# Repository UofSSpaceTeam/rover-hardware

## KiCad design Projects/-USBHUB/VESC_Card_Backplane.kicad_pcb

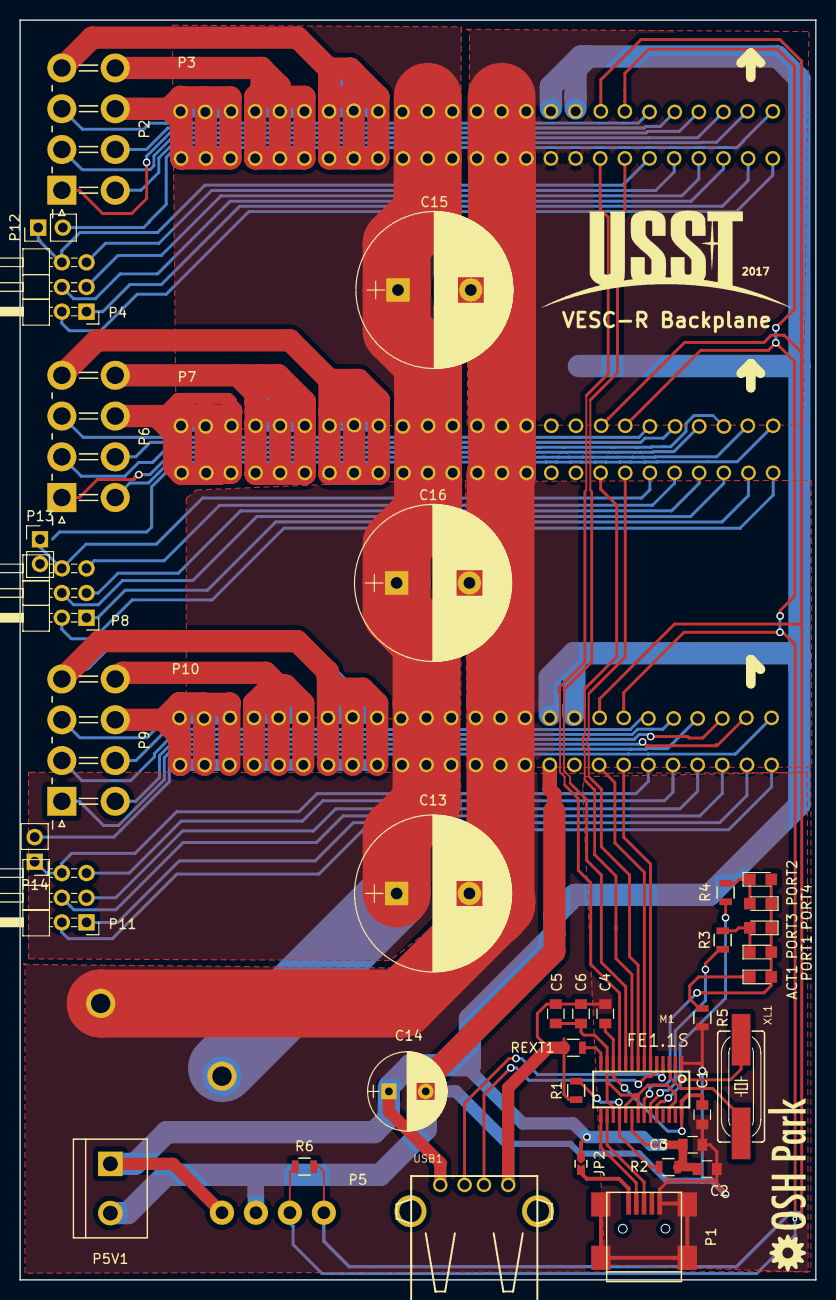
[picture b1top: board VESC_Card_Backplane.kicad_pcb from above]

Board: 2 copper layers, 82.0 x 129.8 mm, 42 parts (1 on the bottom side), 74 nets.

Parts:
ACT1: LED_0805
C1, C2, C5: 10uF; C_0805
C3, C4, C6: 0.1uF; C_0805
C13, C15, C16: 2200u; CP_Radial_D16.0mm_P7.50mm
C14: 100u; CP_Radial_D8.0mm_P3.80mm
JP2: J; J_0603
M1: FE1.1S; FE1.1S_SSOP-28
P1: USB_OTG; USB_Mini-B
P2, P6, P9: EC90_Flat; Molex_MiniFit-JR-5569-08A2_2x04x4.20mm_Angled_Overhang
P3, P7, P10: AMP17614426-2_EDGE; TE2007088-1_Backplane2
P4, P8, P11: CONN_01X06; Pin_Header_Angled_2x03_Pitch2.54mm
P5: CONN_01X04; Molex_39502_1004R
P5V1: CONN_01X02; Molex_39531_1002
P12, P13, P14: CONN_01X02; Pin_Header_Straight_1x02_Pitch2.54mm
PBAT1: CONN_01X02; Phoenix_Contact_PLA5
PORT1, PORT2, PORT3, PORT4: LED_0805
R1: 100K; R_0805
R2: 47K; R_0805
R3, R4, R5: 330; R_0805
R6: 120; R_0805
REXT1: 2.7K; R_0805
USB1: USB-TYPA; USB_A_PTH_AMP787616-1
XL1: 12MHz; HC49UP_SMT_Crystal

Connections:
+5V: C2.1, C3.1, C14.1, JP2.1, M1.20, P3.6, P3.7, P5.1, P5V1.1, P7.6, P7.7, P10.6, P10.7, R2.1, USB1.VBUS
/CANH: P3.8, P5.4, P7.8, P10.8, R6.2
/CAN_Bus/CANL: P3.9, P5.3, P7.9, P10.9, R6.1
/DM_4: M1.4, USB1.D-
/DP_4: M1.5, USB1.D+
/Motor_Controller_A/GND_AUX: P3.21, P4.6, P12.1
/Motor_Controller_A/H1: P2.1, P3.12
/Motor_Controller_A/H2: P2.2, P3.13
/Motor_Controller_A/H3: P2.5, P3.14
/Motor_Controller_A/W: P2.7, P3.1, P3.30
/Motor_Controller_A/X: P2.8, P3.2, P3.29
/Motor_Controller_A/Y: P2.4, P3.3, P3.28
/Motor_Controller_B/GND_AUX: P7.21, P8.6, P13.1
/Motor_Controller_B/H1: P6.1, P7.12
/Motor_Controller_B/H2: P6.2, P7.13
/Motor_Controller_B/H3: P6.5, P7.14
/Motor_Controller_B/W: P6.7, P7.1, P7.30
/Motor_Controller_B/X: P6.8, P7.2, P7.29
/Motor_Controller_B/Y: P6.4, P7.3, P7.28
/Motor_Controller_C/GND_AUX: P10.21, P11.6, P14.1
/Motor_Controller_C/H1: P9.1, P10.12
/Motor_Controller_C/H2: P9.2, P10.13
/Motor_Controller_C/H3: P9.5, P10.14
/Motor_Controller_C/W: P9.7, P10.1, P10.30
/Motor_Controller_C/X: P9.8, P10.2, P10.29
/Motor_Controller_C/Y: P9.4, P10.3, P10.28
/PGND: C13.2, C15.2, C16.2, P3.5, P3.24, P3.25, P3.26, P7.5, P7.24, P7.25, P7.26, P10.5, P10.26, PBAT1.2
/USB_DM_1: M1.10, P3.22
/USB_DM_2: M1.8, P7.22
/USB_DM_3: M1.6, P10.22
/USB_DP_1: M1.11, P3.23
/USB_DP_2: M1.9, P7.23
/USB_DP_3: M1.7, P10.23
/USB_Hub/DM_U: M1.15, P1.2
/USB_Hub/DP_U: M1.16, P1.3
/USB_Hub/N$1: M1.14, REXT1.2
/USB_Hub/N$6: PORT2.1, PORT4.2, R4.2
/USB_Hub/N$7: M1.2, XL1.2
/USB_Hub/N$8: C1.1, C4.1, M1.12, M1.28
/USB_Hub/N$9: M1.3, XL1.1
/USB_Hub/N$13: M1.18, R1.1, R2.2
/USB_Hub/N$20: PORT1.1, PORT3.2, R3.2
/USB_Hub/N$22: ACT1.1, R5.1
/USB_Hub/N$23: M1.23, R3.1
/USB_Hub/N$24: M1.24, R4.1
/USB_Hub/N$25: ACT1.2, M1.22, PORT1.2, PORT2.2, PORT3.1, PORT4.1
/VBAT: C13.1, C15.1, C16.1, P3.4, P3.27, P7.4, P7.27, P10.4, P10.27, PBAT1.1
GND: C1.2, C2.2, C3.2, C4.2, C5.2, C6.2, C14.2, M1.1, P1.5, P1.6, P5.2, P5V1.2, P10.24, P10.25, R1.2, R5.2, REXT1.1, USB1.GND
unnamed: JP2.2, P1.1
unnamed: P2.3, P3.10
unnamed: P2.6, P3.11
unnamed: P3.16, P4.2
unnamed: P3.17, P4.1
unnamed: P3.18, P4.4
unnamed: P3.19, P4.3
unnamed: P3.20, P4.5
unnamed: P6.3, P7.10
unnamed: P6.6, P7.11
unnamed: P7.16, P8.2
unnamed: P7.17, P8.1
unnamed: P7.18, P8.4
unnamed: P7.19, P8.3
unnamed: P7.20, P8.5
unnamed: P9.3, P10.10
unnamed: P9.6, P10.11
unnamed: P10.15, P14.2
unnamed: P10.16, P11.2
unnamed: P10.17, P11.1
unnamed: P10.18, P11.4
unnamed: P10.19, P11.3
unnamed: P10.20, P11.5
unnamed: P3.15, P12.2
unnamed: P7.15, P13.2
VDD: C5.1, C6.1, M1.13, M1.17, M1.19, M1.21, M1.26

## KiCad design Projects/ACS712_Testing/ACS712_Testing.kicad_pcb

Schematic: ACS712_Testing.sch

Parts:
P1: CONN_01X04; Pin_Header_Straight_1x04_Pitch2.54mm
R1: 10k; R_0805_HandSoldering
TH1: THERMISTOR; R_0805_HandSoldering
W1, W2: TEST_1P; Testpad_large

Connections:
+3V3: P1.1, TH1.1; also elsewhere on the board
/ACS712/ALL_I+: W1.1, W2.1; also elsewhere on the board
/ACS712/ISENSE_OUT: P1.3; also elsewhere on the board
GND: P1.4, R1.2; also elsewhere on the board
unnamed: P1.2, R1.1, TH1.2

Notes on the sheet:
To Do: - Power Connectors (In and Out) - Logic and Power Connector (3V3 and GND and ISENSE_OUT) - NTC Temperature Sensor Circuit (http://www.petervis.com/GCSE_Design_and_Technology_Electronic_Products/Potential_Divider/Potential_Divider_with_Thermistor.html) - Connect I+ and I- to Power

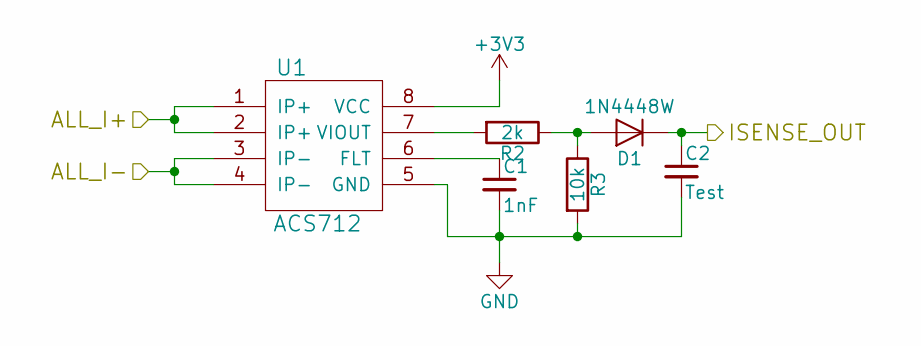
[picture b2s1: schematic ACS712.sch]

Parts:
C1: 1nF; C_1210
C2: Test; C_1210
D1: 1N4448W; D_SOD-123
R2: 2k; R_0805_HandSoldering
R3: 10k; R_0805_HandSoldering
U1: ACS712; SOIC-8_3.9x4.9mm_Pitch1.27mm

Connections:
+3V3: U1.8 (VCC); also elsewhere on the board
/ACS712/ALL_I+: U1.1 (IP+), U1.2 (IP+), U1.3 (IP-), U1.4 (IP-); also elsewhere on the board
/ACS712/ISENSE_OUT: C2.1, D1.1 (K); also elsewhere on the board
GND: C1.2, C2.2, R3.2, U1.5 (GND); also elsewhere on the board
unnamed: C1.1, U1.6 (FLT)
unnamed: D1.2 (A), R2.1, R3.1
unnamed: R2.2, U1.7 (VIOUT)

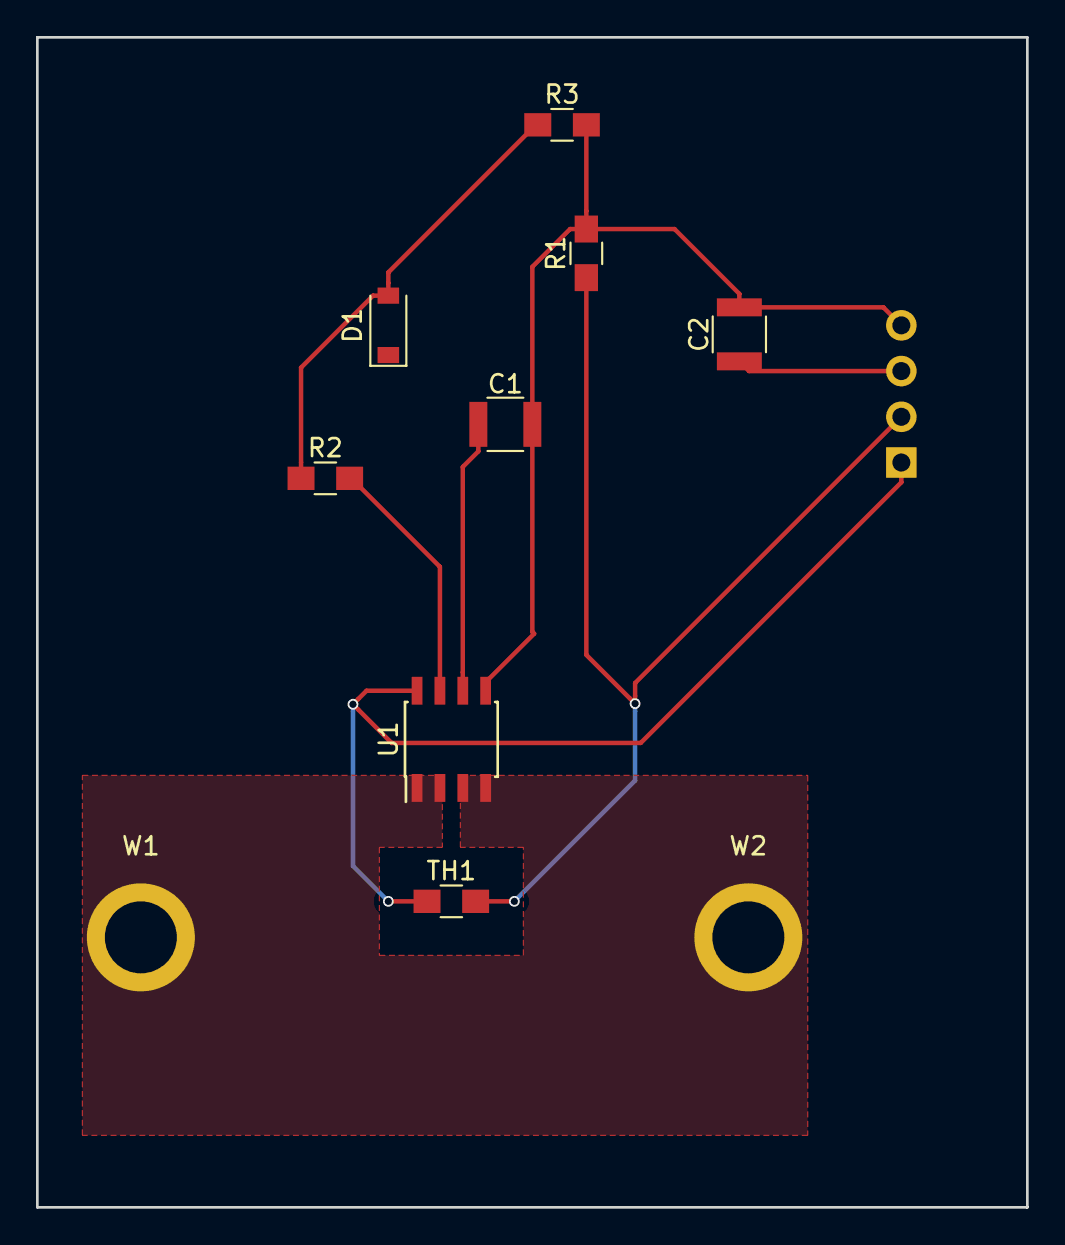
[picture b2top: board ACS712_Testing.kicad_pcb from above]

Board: 2 copper layers, 55.0 x 65.0 mm, 11 parts (1 on the bottom side), 8 nets.

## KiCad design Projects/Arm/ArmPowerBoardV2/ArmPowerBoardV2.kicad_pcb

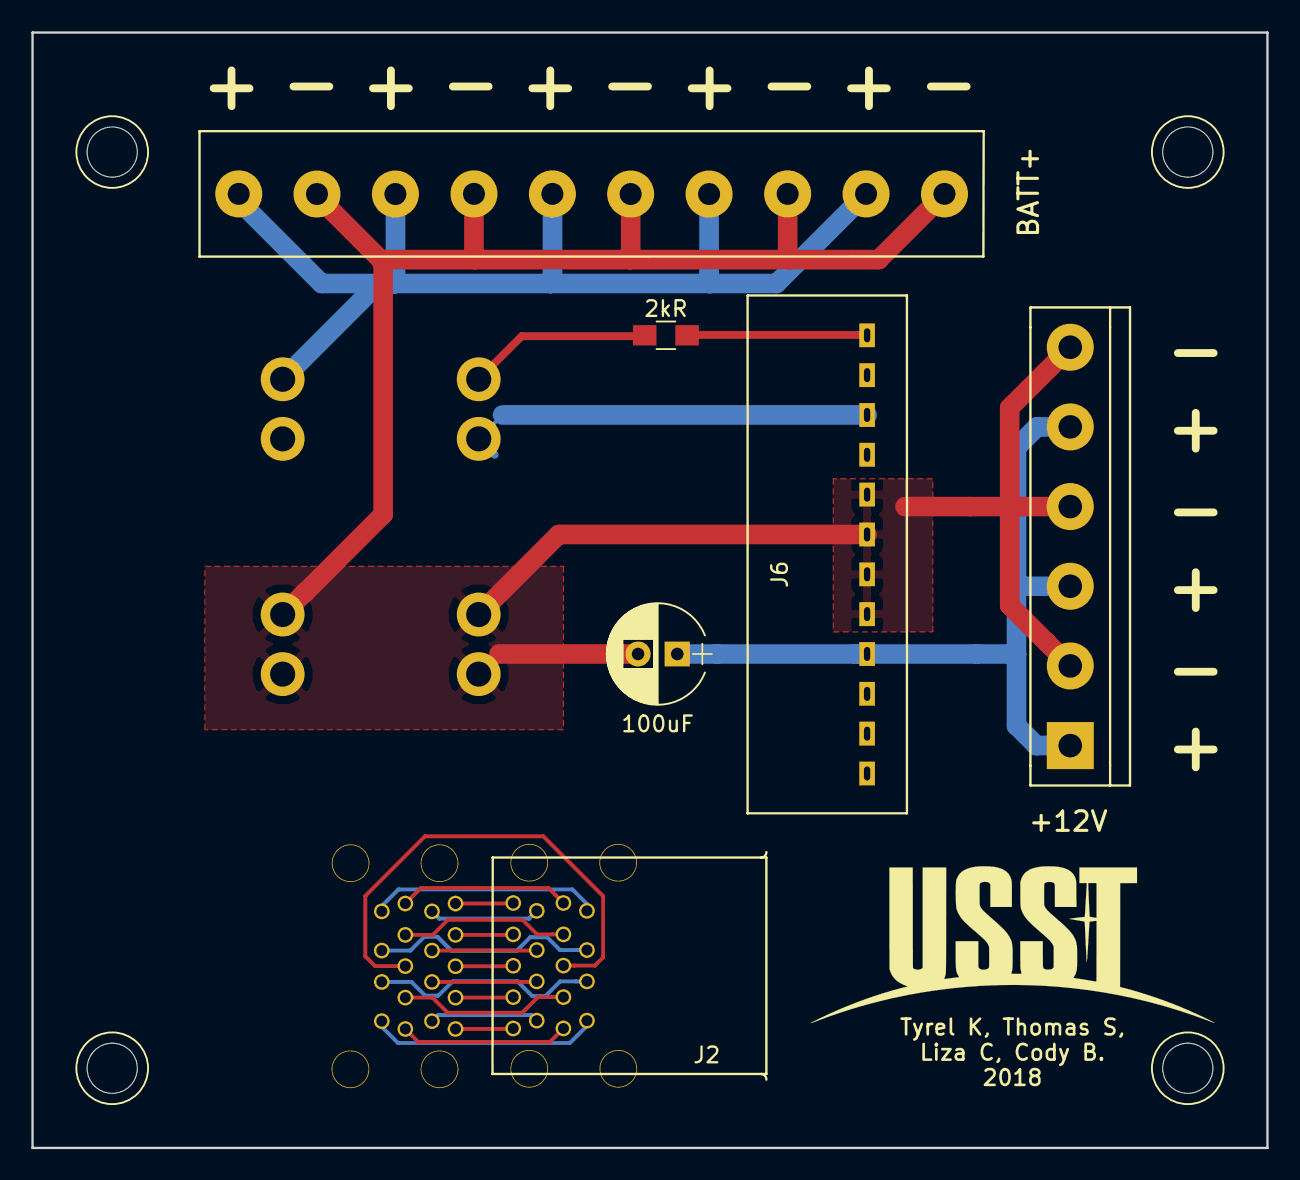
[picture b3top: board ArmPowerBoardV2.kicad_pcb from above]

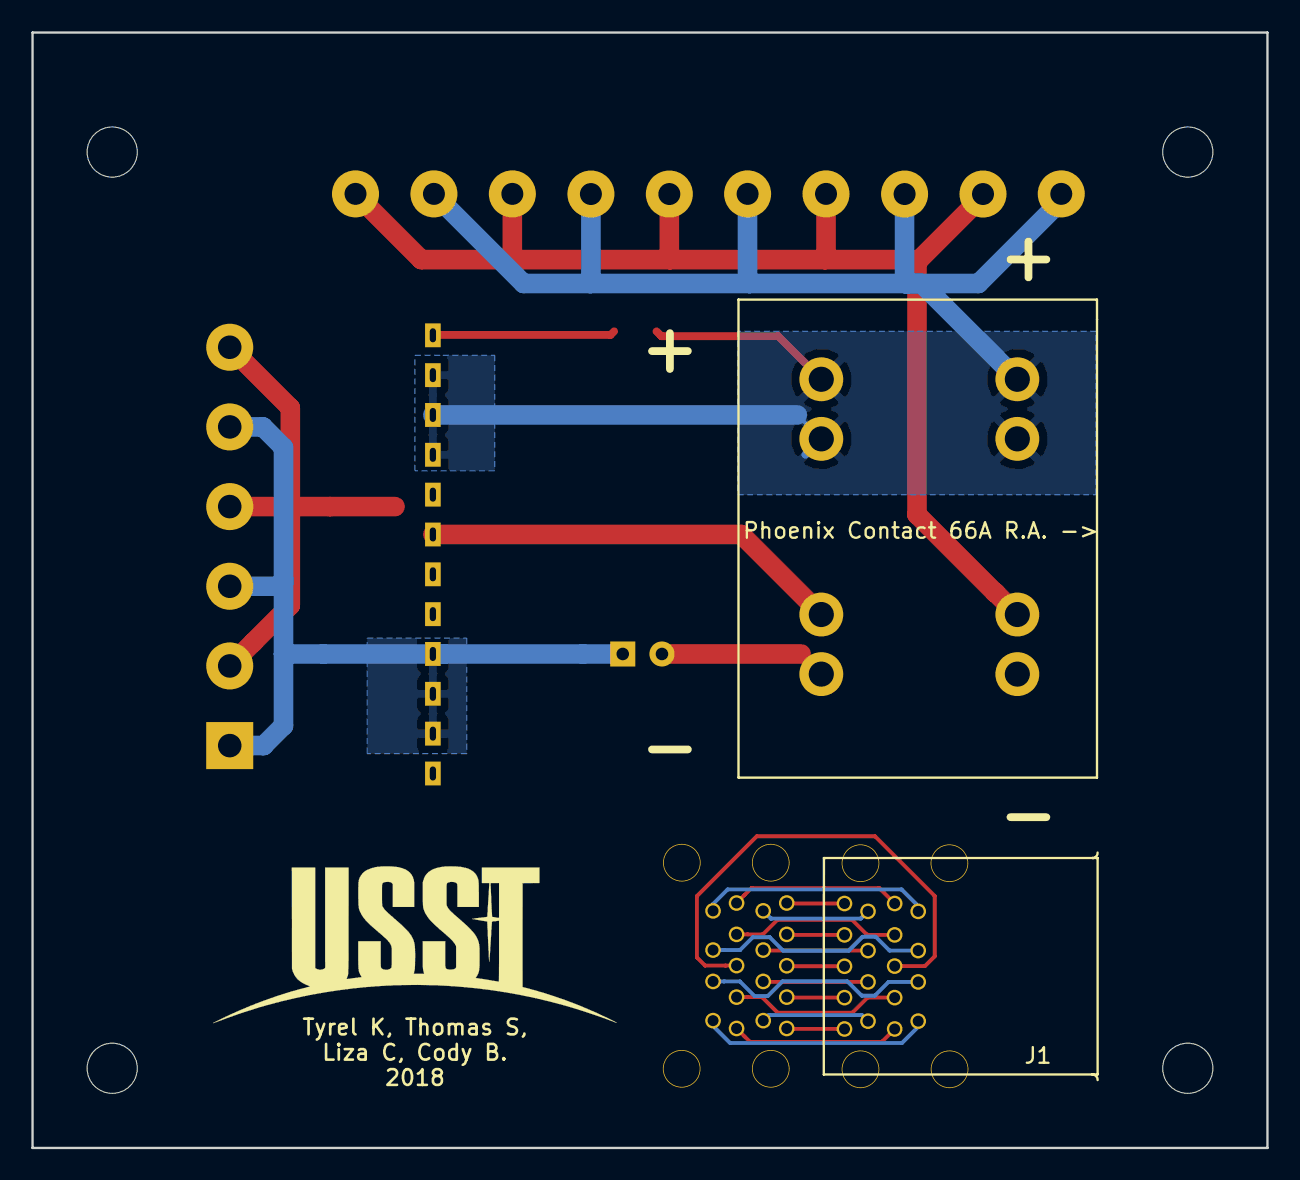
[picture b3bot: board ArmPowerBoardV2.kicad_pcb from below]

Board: 2 copper layers, 78.7 x 71.1 mm, 8 parts (2 on the bottom side), 22 nets.

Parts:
2kR: 2kR; R_0805_HandSoldering
100uF: 100uF; CP_Radial_D6.3mm_P2.50mm
+12V: 1x6 Conn +12V; TerminalBlock_Pheonix_PT-5mm_6pol
BATT+: 1x10 Conn Batt+; Phoenix_Contact_Terminal_Block_1x10_1935242
J1, J2: USB 3.0 A Stacked; USB-A_3.0_Stacked_WM10420-ND
J6: R-6212P 12V DC Regulator; R-6212P_14-34VDC-12VDC_Converter
Phoenix Contact 66A R.A. ->: Phoenix Contact Batt; Phoenix_Contact_1770539

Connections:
+12V: 100uF.1, +12V.1, +12V.3, +12V.5, J6.9, J6.10, J6.11
BATT+: 2kR.1, BATT+.1, BATT+.3, BATT+.5, BATT+.7, BATT+.9, J6.2, J6.3, J6.4, Phoenix Contact 66A R.A. ->.1
GND: 100uF.2, +12V.2, +12V.4, +12V.6, BATT+.2, BATT+.4, BATT+.6, BATT+.8, BATT+.10, J6.5, J6.6, J6.7, J6.8, Phoenix Contact 66A R.A. ->.2
unnamed: J1.1, J2.1
unnamed: J1.2, J2.2
unnamed: J1.3, J2.3
unnamed: J1.4, J2.4
unnamed: J1.5, J2.5
unnamed: J1.6, J2.6
unnamed: J1.7, J2.7
unnamed: J1.8, J2.8
unnamed: J1.9, J2.9
unnamed: J1.10, J2.10
unnamed: J1.11, J2.11
unnamed: J1.12, J2.12
unnamed: J1.13, J2.13
unnamed: J1.14, J2.14
unnamed: J1.15, J2.15
unnamed: J1.16, J2.16
unnamed: J1.17, J2.17
unnamed: J1.18, J2.18
unnamed: 2kR.2, J6.1

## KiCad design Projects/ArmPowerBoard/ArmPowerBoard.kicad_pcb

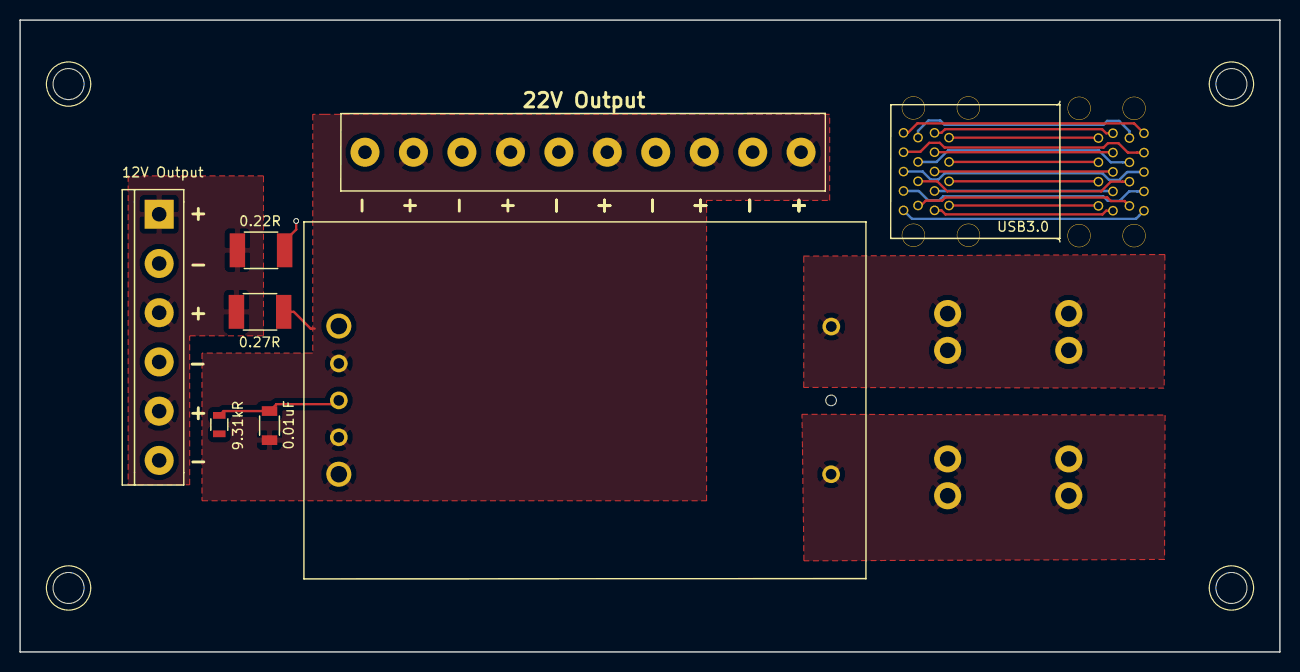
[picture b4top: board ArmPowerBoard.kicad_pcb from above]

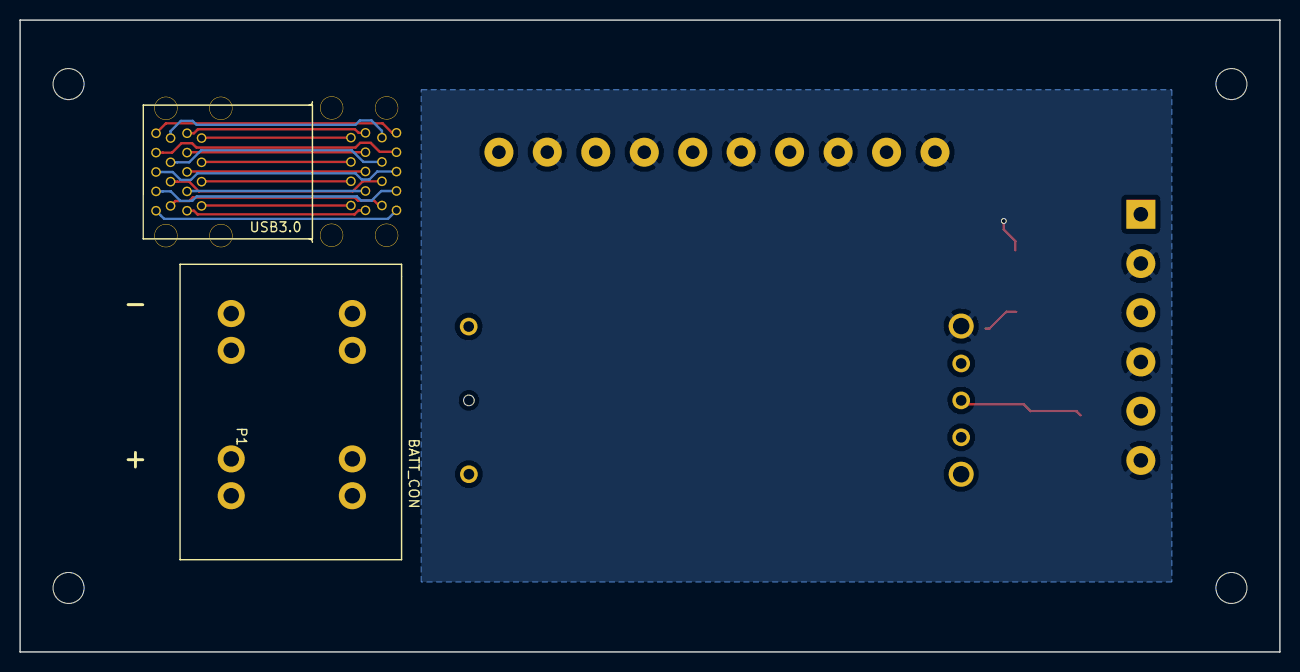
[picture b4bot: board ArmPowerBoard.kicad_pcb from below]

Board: 2 copper layers, 130.0 x 65.2 mm, 10 parts (2 on the bottom side), 24 nets.

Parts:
0.01uF: 0.01uF; C_1206
0.22R: 0.22; R_1812
0.27R: 0.27; R_1812
9.31kR: 9.3182; R_0805
J1: 22V Output; Phoenix_Contact_Terminal_Block_1x10_1935242
J2: 12V Output; TerminalBlock_Pheonix_PT-5mm_6pol
P1: BATT_CON; Phoenix_Contact_1770539
U1: IQL24040A050V-009-R-ND; IQL24040A050V_Power_Supply
USB3.0, USB3.0#2: CONN_02X09; USB-A_3.0_Stacked_WM10420-ND

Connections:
/-Vout: 0.22R.1, J1.2, J1.4, J1.6, J1.8, J1.10, J2.2, J2.4, J2.6, U1.4
GND: P1.1, U1.3
unnamed: 0.22R.2, 0.27R.1, J2.1, J2.3, J2.5
unnamed: 0.01uF.1, 0.27R.2, J1.1, J1.3, J1.5, J1.7, J1.9, U1.7, U1.8
unnamed: 0.01uF.2, 9.31kR.2, U1.6
unnamed: P1.2, U1.1
unnamed: USB3.0.1, USB3.0#2.1
unnamed: USB3.0.2, USB3.0#2.2
unnamed: USB3.0.3, USB3.0#2.3
unnamed: USB3.0.4, USB3.0#2.4
unnamed: USB3.0.5, USB3.0#2.5
unnamed: USB3.0.6, USB3.0#2.6
unnamed: USB3.0.7, USB3.0#2.7
unnamed: USB3.0.8, USB3.0#2.8
unnamed: USB3.0.9, USB3.0#2.9
unnamed: USB3.0.10, USB3.0#2.10
unnamed: USB3.0.11, USB3.0#2.11
unnamed: USB3.0.12, USB3.0#2.12
unnamed: USB3.0.13, USB3.0#2.13
unnamed: USB3.0.14, USB3.0#2.14
unnamed: USB3.0.15, USB3.0#2.15
unnamed: USB3.0.16, USB3.0#2.16
unnamed: USB3.0.17, USB3.0#2.17
unnamed: USB3.0.18, USB3.0#2.18

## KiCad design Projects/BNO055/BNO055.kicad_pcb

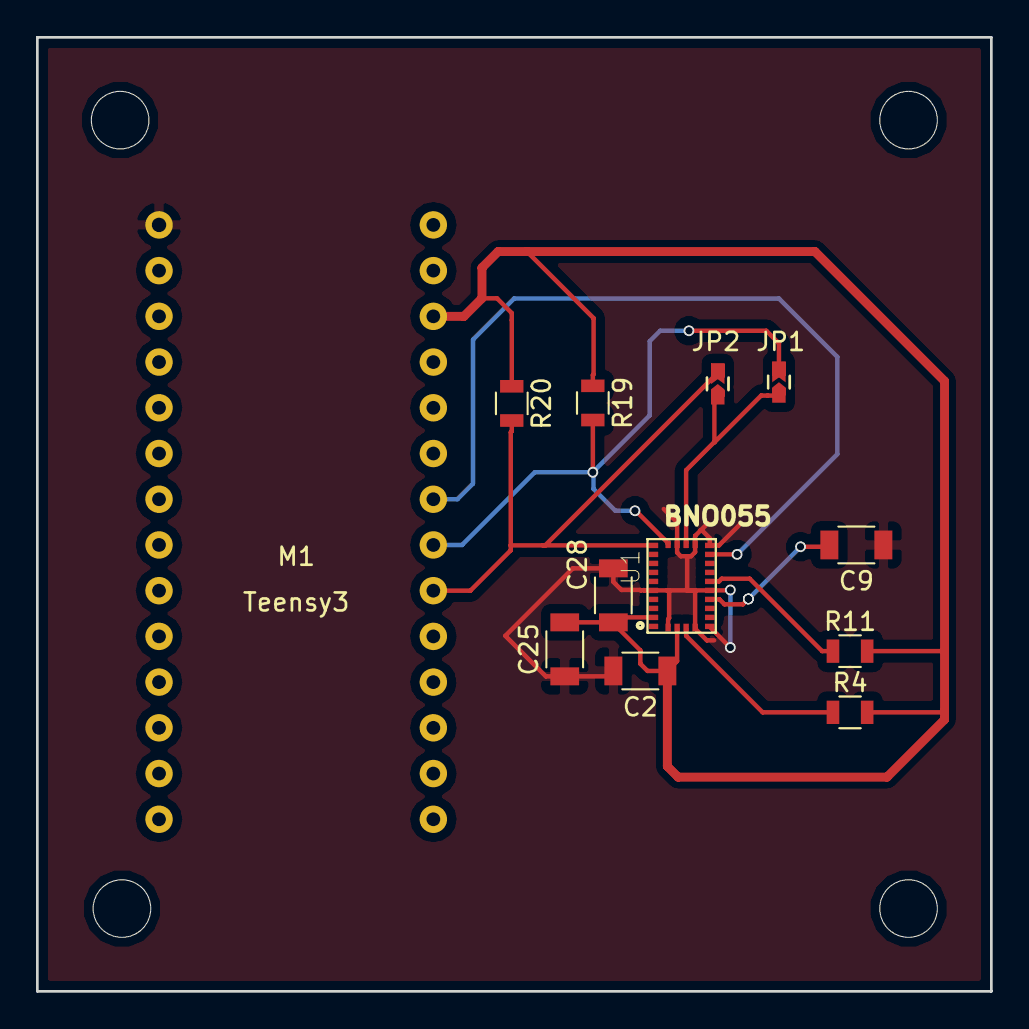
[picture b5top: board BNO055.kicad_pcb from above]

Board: 2 copper layers, 53.0 x 53.0 mm, 12 parts (0 on the bottom side), 9 nets.

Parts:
C2, C9: 100nF; C_1206
C25: 6.8nF; C_1206
C28: 120nF; C_1206
JP1: Jumper_NC_Small; J_0603
JP2: Jumper_NO_Small; J_0603
M1: Teensy3; Teensy_3.2_NoTail
R4, R11: 10k; R_0805
R19: 3.3k; R_0805
R20: 2.7k; R_0805
U1: BNO055; LGA28R50P4X10_380X520X100

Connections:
+3V3: C2.2, C25.1, C28.1, M1.3v3, R4.2, R11.2, R19.1, R20.1, U1.3, U1.28
/INT: M1.20, U1.14
/SCL: JP1.2, M1.19, R19.2, U1.19
/SDA: JP2.2, M1.18, R20.2, U1.20
GND: C2.1, C9.1, C25.2, C28.2, M1.GND, U1.2, U1.5, U1.6, U1.10, U1.15, U1.16, U1.18, U1.25
unnamed: C9.2, U1.9
unnamed: JP1.1, JP2.1, U1.17
unnamed: R4.1, U1.4
unnamed: R11.1, U1.11

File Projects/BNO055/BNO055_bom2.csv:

"C2, C9"	"100nF"	"Capacitors_SMD:C_1206"	""	""	""		2
"C25"	"6.8nF"	"Capacitors_SMD:C_1206"	""	""	""		1
"C28"	"120nF"	"Capacitors_SMD:C_1206"	""	""	""		1
"JP1"	"Jumper_NC_Small"	"USST-footprints:J_0603"	""	""	""		1
"JP2"	"Jumper_NO_Small"	"USST-footprints:J_0603"	""	""	""		1
"M1"	"Teensy3"	"USST-footprints:Teensy_3.2_NoTail"	""	""	""		1
"R4, R11"	"10k"	"Resistors_SMD:R_0805"	""	""	""		2
"R19"	"3.3k"	"Resistors_SMD:R_0805"	""	""	""		1
"R20"	"2.7k"	"Resistors_SMD:R_0805"	""	""	""		1
"U1"	"BNO055"	"BNO055:LGA28R50P4X10_380X520X100"	""	""	""	8.19 USD	1

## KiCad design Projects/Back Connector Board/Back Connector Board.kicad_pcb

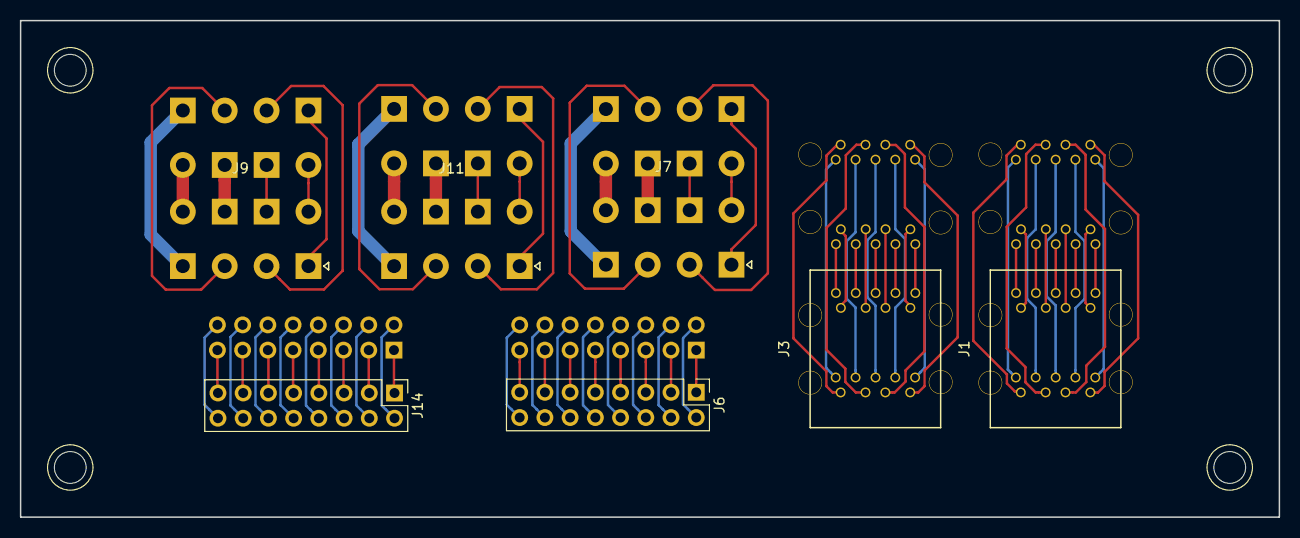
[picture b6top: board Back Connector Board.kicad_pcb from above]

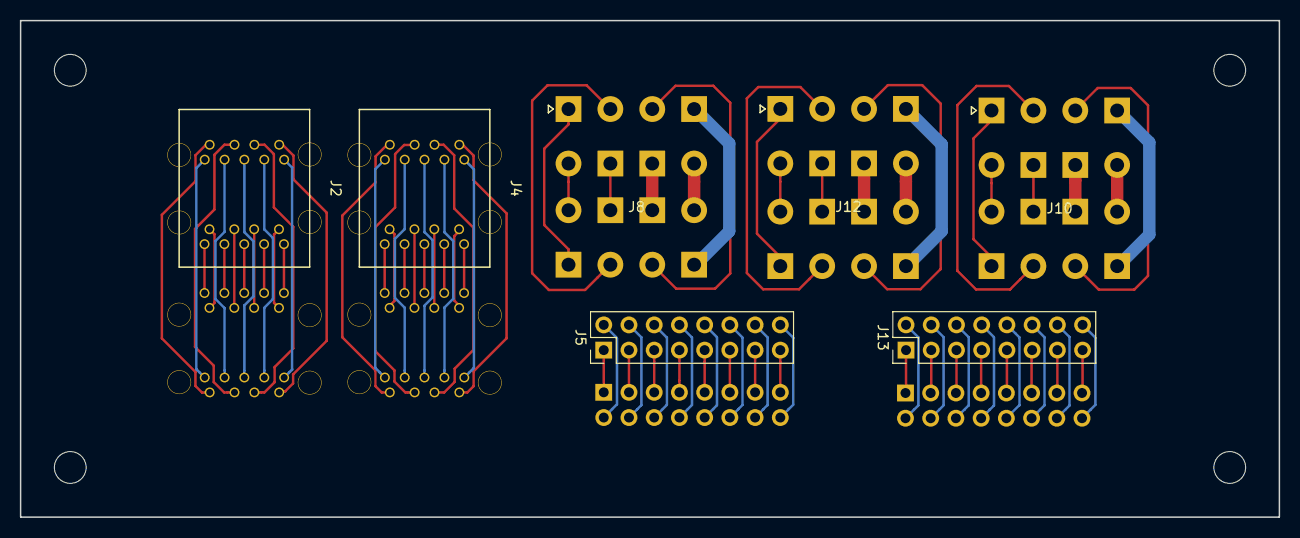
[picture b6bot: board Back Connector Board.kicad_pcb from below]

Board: 2 copper layers, 126.8 x 50.0 mm, 14 parts (7 on the bottom side), 92 nets.

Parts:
J1, J2, J3, J4: Conn_02x09_Odd_Even; USBA_3.0_Stacked_Vertical-Molex_48409
J5, J6, J13, J14: Conn_02x08_Odd_Even; Pin_Header_Straight_2x08_Pitch2.54mm
J7, J8, J9, J10, J11, J12: Molex_MiniFit_02x04; Molex_MiniFit-JR_5566-08A_02x04x4.2_Vertical

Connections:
unnamed: J1.1, J2.1
unnamed: J1.2, J2.2
unnamed: J1.3, J2.3
unnamed: J1.4, J2.4
unnamed: J1.5, J2.5
unnamed: J1.6, J2.6
unnamed: J1.7, J2.7
unnamed: J1.8, J2.8
unnamed: J1.9, J2.9
unnamed: J1.10, J2.10
unnamed: J1.11, J2.11
unnamed: J1.12, J2.12
unnamed: J1.13, J2.13
unnamed: J1.14, J2.14
unnamed: J1.15, J2.15
unnamed: J1.16, J2.16
unnamed: J1.17, J2.17
unnamed: J1.18, J2.18
unnamed: J3.1, J4.1
unnamed: J3.2, J4.2
unnamed: J3.3, J4.3
unnamed: J3.4, J4.4
unnamed: J3.5, J4.5
unnamed: J3.6, J4.6
unnamed: J3.7, J4.7
unnamed: J3.8, J4.8
unnamed: J3.9, J4.9
unnamed: J3.10, J4.10
unnamed: J3.11, J4.11
unnamed: J3.12, J4.12
unnamed: J3.13, J4.13
unnamed: J3.14, J4.14
unnamed: J3.15, J4.15
unnamed: J3.16, J4.16
unnamed: J3.17, J4.17
unnamed: J3.18, J4.18
unnamed: J5.1, J6.1
unnamed: J5.2, J6.2
unnamed: J5.3, J6.3
unnamed: J5.4, J6.4
unnamed: J5.5, J6.5
unnamed: J5.6, J6.6
unnamed: J5.7, J6.7
unnamed: J5.8, J6.8
unnamed: J5.9, J6.9
unnamed: J5.10, J6.10
unnamed: J5.11, J6.11
unnamed: J5.12, J6.12
unnamed: J5.13, J6.13
unnamed: J5.14, J6.14
unnamed: J5.15, J6.15
unnamed: J5.16, J6.16
unnamed: J7.1, J8.1
unnamed: J7.2, J8.2
unnamed: J7.3, J8.3
unnamed: J7.4, J8.4
unnamed: J7.5, J8.5
unnamed: J7.6, J8.6
unnamed: J7.7, J8.7
unnamed: J7.8, J8.8
unnamed: J9.1, J10.1
unnamed: J9.2, J10.2
unnamed: J9.3, J10.3
unnamed: J9.4, J10.4
unnamed: J9.5, J10.5
unnamed: J9.6, J10.6
unnamed: J9.7, J10.7
unnamed: J9.8, J10.8
unnamed: J11.1, J12.1
unnamed: J11.2, J12.2
unnamed: J11.3, J12.3
unnamed: J11.4, J12.4
unnamed: J11.5, J12.5
unnamed: J11.6, J12.6
unnamed: J11.7, J12.7
unnamed: J11.8, J12.8
unnamed: J13.1, J14.1
unnamed: J13.2, J14.2
unnamed: J13.3, J14.3
unnamed: J13.4, J14.4
unnamed: J13.5, J14.5
unnamed: J13.6, J14.6
unnamed: J13.7, J14.7
unnamed: J13.8, J14.8
unnamed: J13.9, J14.9
unnamed: J13.10, J14.10
unnamed: J13.11, J14.11
unnamed: J13.12, J14.12
unnamed: J13.13, J14.13
unnamed: J13.14, J14.14
unnamed: J13.15, J14.15
unnamed: J13.16, J14.16
